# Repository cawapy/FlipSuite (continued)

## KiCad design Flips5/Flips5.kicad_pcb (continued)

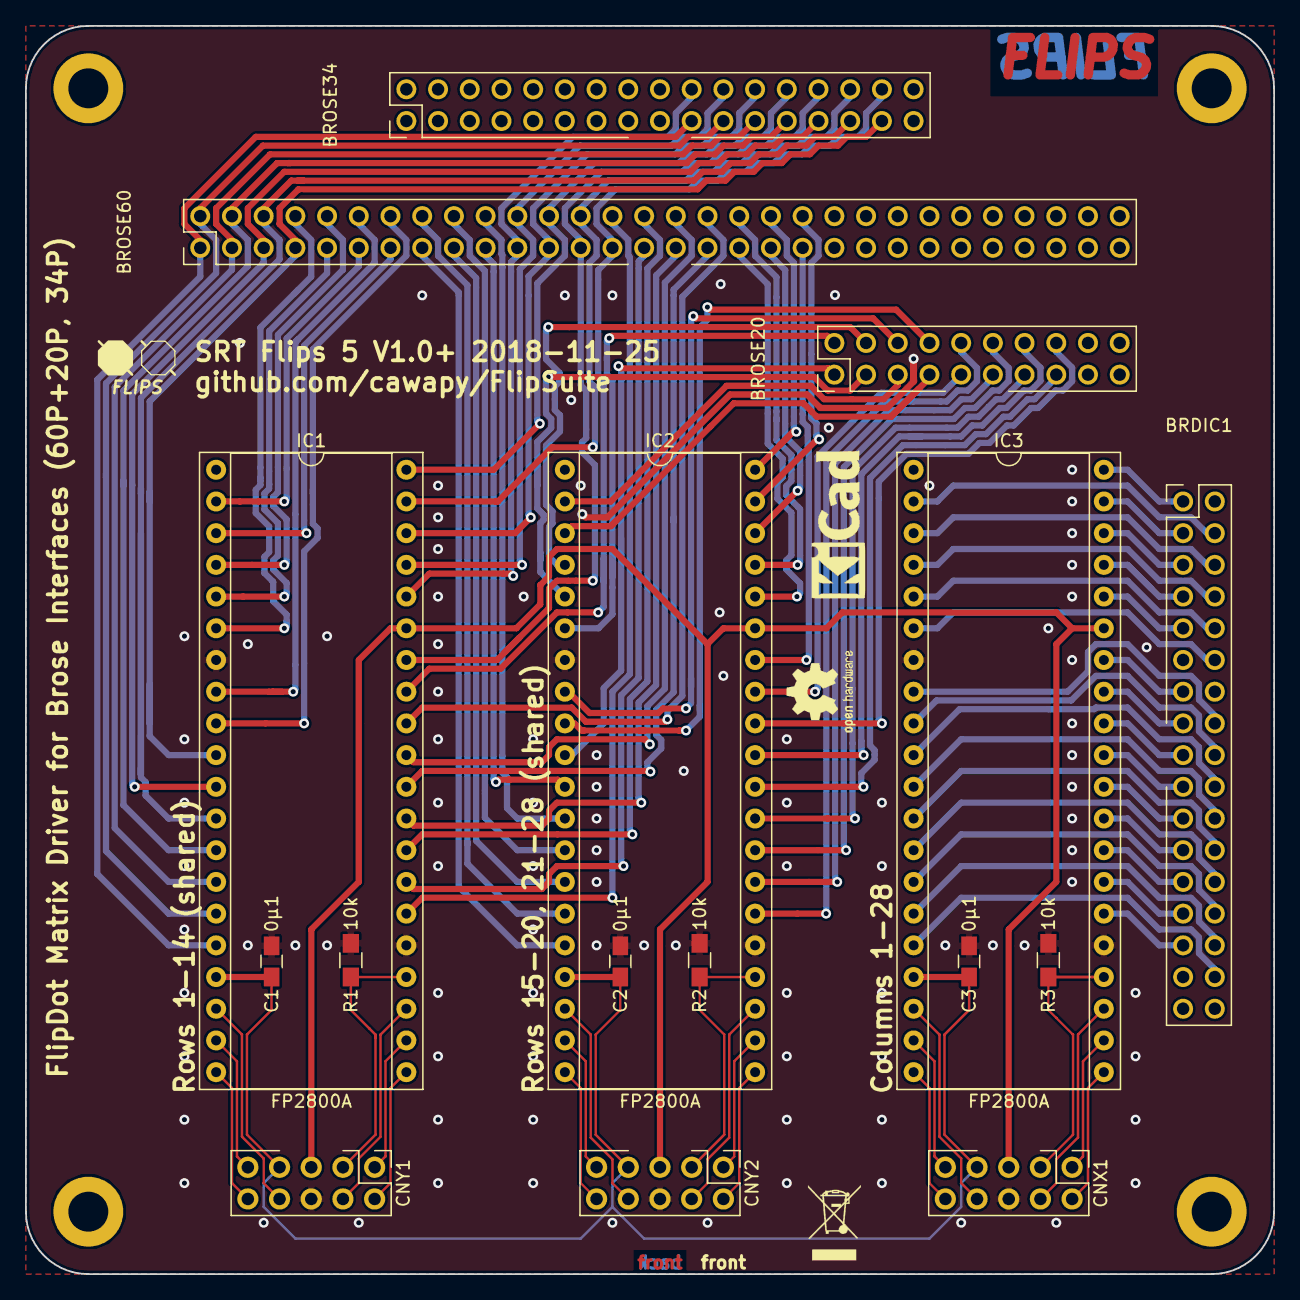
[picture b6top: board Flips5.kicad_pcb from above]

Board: 2 copper layers, 100.0 x 100.0 mm, 16 parts (0 on the bottom side), 108 nets.

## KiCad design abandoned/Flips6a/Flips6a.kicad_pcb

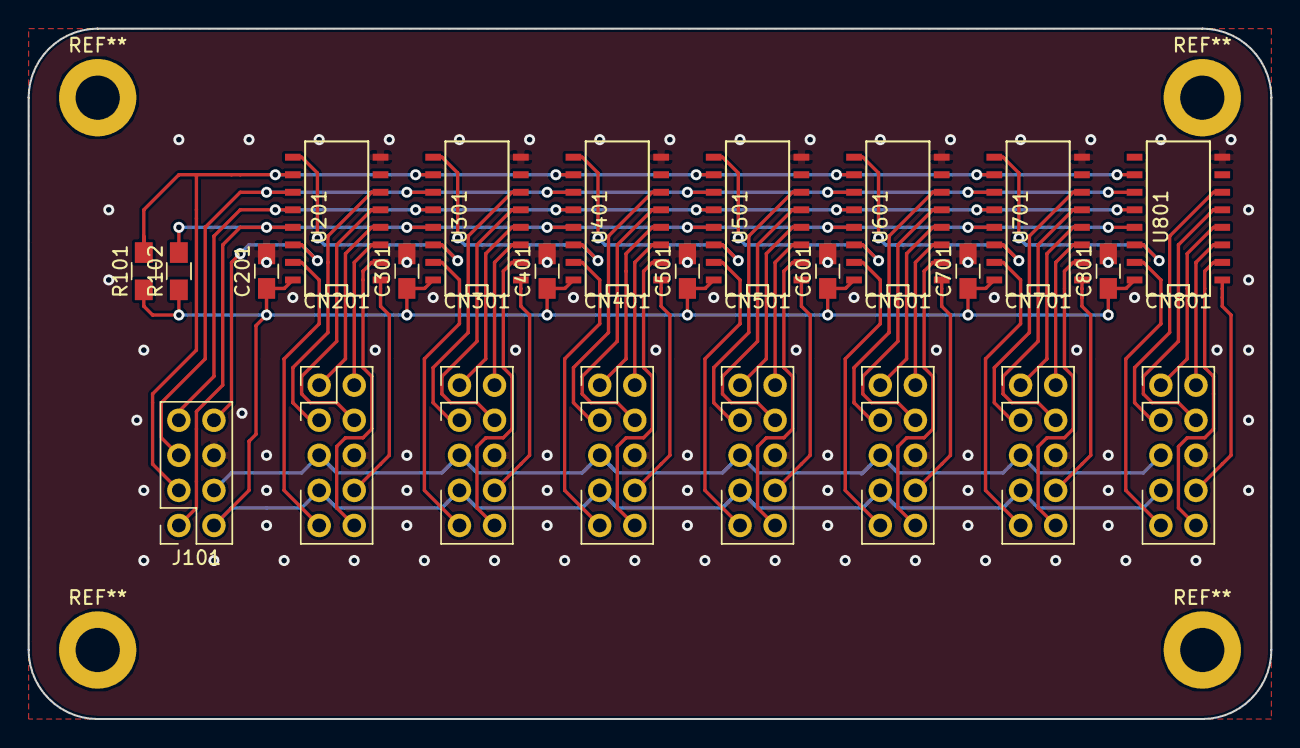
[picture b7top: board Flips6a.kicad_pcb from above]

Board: 2 copper layers, 90.0 x 50.0 mm, 24 parts (0 on the bottom side), 63 nets.

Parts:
C201, C301, C401, C501, C601, C701, C801: 0u1; C_0805_HandSoldering
CN201, CN301, CN401, CN501, CN601, CN701, CN801: UFP2810; Pin_Header_Straight_Shrouded_2x05_Pitch2.54mm
J101: Conn_02x04_Odd_Even; Socket_Strip_Straight_2x04_Pitch2.54mm
R101, R102: 10K; R_0805_HandSoldering
U201, U301, U401, U501, U601, U701, U801: 74HCT595; SO-16-N

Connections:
+5V: C201.1, C301.1, C401.1, C501.1, C601.1, C701.1, C801.1, CN201.7, CN301.7, CN401.7, CN501.7, CN601.7, CN701.7, CN801.7, J101.2, R101.1, R102.1, U201.16, U301.16, U401.16, U501.16, U601.16, U701.16, U801.16
+12V: CN201.5, CN301.5, CN401.5, CN501.5, CN601.5, CN701.5, CN801.5, J101.4
/ShiftRegister2/A0: CN201.9, U201.15
/ShiftRegister2/A1: CN201.8, U201.1
/ShiftRegister2/A2: CN201.10, U201.2
/ShiftRegister2/B0: CN201.2, U201.3
/ShiftRegister2/B1: CN201.1, U201.4
/ShiftRegister2/DATA: CN201.4, U201.5
/ShiftRegister2/DIN: J101.8, U201.14
/ShiftRegister2/EN: CN201.3, U201.6
/ShiftRegister3/A0: CN301.9, U301.15
/ShiftRegister3/A1: CN301.8, U301.1
/ShiftRegister3/A2: CN301.10, U301.2
/ShiftRegister3/B0: CN301.2, U301.3
/ShiftRegister3/B1: CN301.1, U301.4
/ShiftRegister3/DATA: CN301.4, U301.5
/ShiftRegister3/DIN: U201.9, U301.14
/ShiftRegister3/EN: CN301.3, U301.6
/ShiftRegister4/A0: CN401.9, U401.15
/ShiftRegister4/A1: CN401.8, U401.1
/ShiftRegister4/A2: CN401.10, U401.2
/ShiftRegister4/B0: CN401.2, U401.3
/ShiftRegister4/B1: CN401.1, U401.4
/ShiftRegister4/DATA: CN401.4, U401.5
/ShiftRegister4/DIN: U301.9, U401.14
/ShiftRegister4/EN: CN401.3, U401.6
/ShiftRegister5/A0: CN501.9, U501.15
/ShiftRegister5/A1: CN501.8, U501.1
/ShiftRegister5/A2: CN501.10, U501.2
/ShiftRegister5/B0: CN501.2, U501.3
/ShiftRegister5/B1: CN501.1, U501.4
/ShiftRegister5/DATA: CN501.4, U501.5
/ShiftRegister5/DIN: U401.9, U501.14
/ShiftRegister5/EN: CN501.3, U501.6
/ShiftRegister6/A0: CN601.9, U601.15
/ShiftRegister6/A1: CN601.8, U601.1
/ShiftRegister6/A2: CN601.10, U601.2
/ShiftRegister6/B0: CN601.2, U601.3
/ShiftRegister6/B1: CN601.1, U601.4
/ShiftRegister6/DATA: CN601.4, U601.5
/ShiftRegister6/DIN: U501.9, U601.14
/ShiftRegister6/EN: CN601.3, U601.6
/ShiftRegister7/A0: CN701.9, U701.15
/ShiftRegister7/A1: CN701.8, U701.1
/ShiftRegister7/A2: CN701.10, U701.2
/ShiftRegister7/B0: CN701.2, U701.3
/ShiftRegister7/B1: CN701.1, U701.4
/ShiftRegister7/DATA: CN701.4, U701.5
/ShiftRegister7/DIN: U601.9, U701.14
/ShiftRegister7/EN: CN701.3, U701.6
/ShiftRegister8/A0: CN801.9, U801.15
/ShiftRegister8/A1: CN801.8, U801.1
/ShiftRegister8/A2: CN801.10, U801.2
/ShiftRegister8/B0: CN801.2, U801.3
/ShiftRegister8/B1: CN801.1, U801.4
/ShiftRegister8/DATA: CN801.4, U801.5
/ShiftRegister8/DIN: U701.9, U801.14
/ShiftRegister8/EN: CN801.3, U801.6
GND: C201.2, C301.2, C401.2, C501.2, C601.2, C701.2, C801.2, CN201.6, CN301.6, CN401.6, CN501.6, CN601.6, CN701.6, CN801.6, J101.6, U201.8, U301.8, U401.8, U501.8, U601.8, U701.8, U801.8
RCLK: J101.7, U201.12, U301.12, U401.12, U501.12, U601.12, U701.12, U801.12
SRCLK: J101.5, U201.11, U301.11, U401.11, U501.11, U601.11, U701.11, U801.11
~OE: J101.1, R102.2, U201.13, U301.13, U401.13, U501.13, U601.13, U701.13, U801.13
~SRCLR: J101.3, R101.2, U201.10, U301.10, U401.10, U501.10, U601.10, U701.10, U801.10

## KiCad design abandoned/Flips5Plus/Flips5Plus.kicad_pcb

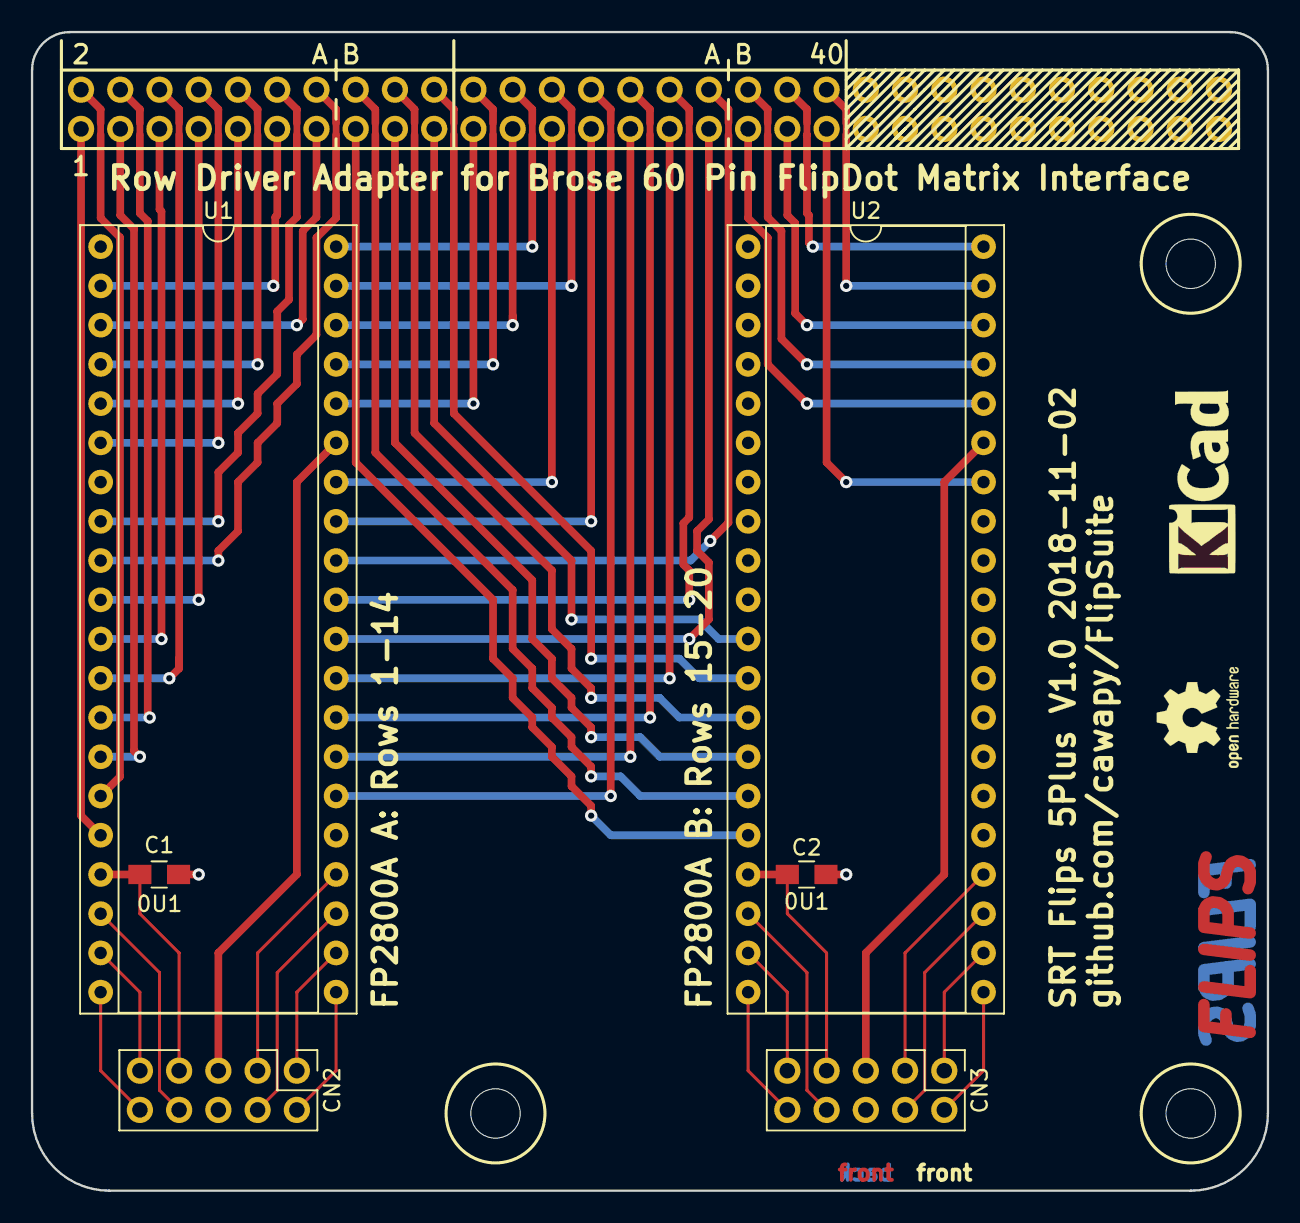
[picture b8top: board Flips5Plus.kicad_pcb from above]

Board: 2 copper layers, 80.0 x 75.0 mm, 7 parts (1 on the bottom side), 60 nets.

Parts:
C1, C2: 0U1; C_0805_HandSoldering
CN1: Conn_02x30_Odd_Even; Socket_Strip_Straight_2x30_Pitch2.54mm
CN2, CN3: UFP2810; Pin_Header_Angle_Shrouded_2x05_Pitch2.54mm
U1, U2: FP2800A; DIP-40_W15.24mm_Socket

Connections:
/L.A0: CN2.9, U1.19
/L.A1: CN2.8, U1.18
/L.A2: CN2.10, U1.20
/L.B0: CN2.2, U1.21
/L.B1: CN2.1, U1.22
/L.EN: CN2.3, U1.24
/L.GND: C1.1, CN2.6, U1.7, U1.25
/L.HV: CN2.5, U1.35
/L.POL: CN2.4, U1.23
/L.VCC: C1.2, CN2.7, U1.17
/R.A0: CN3.9, U2.19
/R.A1: CN3.8, U2.18
/R.A2: CN3.10, U2.20
/R.B0: CN3.2, U2.21
/R.B1: CN3.1, U2.22
/R.EN: CN3.3, U2.24
/R.GND: C2.2, CN3.6, U2.7, U2.25
/R.HV: CN3.5, U2.35
/R.POL: CN3.4, U2.23
/R.VCC: C2.1, CN3.7, U2.17
unnamed: CN1.1, U1.16
unnamed: CN1.2, U1.15
unnamed: CN1.3, U1.14
unnamed: CN1.4, U1.13
unnamed: CN1.5, U1.11
unnamed: CN1.6, U1.12
unnamed: CN1.7, U1.10
unnamed: CN1.8, U1.6
unnamed: CN1.9, U1.5
unnamed: CN1.10, U1.4
unnamed: CN1.11, U1.2
unnamed: CN1.12, U1.8
unnamed: CN1.13, U1.3
unnamed: CN1.14, U1.9
unnamed: CN1.15, U2.16
unnamed: CN1.16, U2.15
unnamed: CN1.17, U2.14
unnamed: CN1.18, U2.13
unnamed: CN1.19, U2.11
unnamed: CN1.20, U2.12
unnamed: CN1.21, U1.36
unnamed: CN1.22, U1.37
unnamed: CN1.23, U1.38
unnamed: CN1.24, U1.40
unnamed: CN1.25, U1.34
unnamed: CN1.26, U1.39
unnamed: CN1.27, U1.33
unnamed: CN1.28, U1.26
unnamed: CN1.29, U1.27
unnamed: CN1.30, U1.28
unnamed: CN1.31, U1.29
unnamed: CN1.32, U1.31
unnamed: CN1.33, U1.30
unnamed: CN1.34, U1.32
unnamed: CN1.35, U2.36
unnamed: CN1.36, U2.37
unnamed: CN1.37, U2.38
unnamed: CN1.38, U2.40
unnamed: CN1.39, U2.34
unnamed: CN1.40, U2.39

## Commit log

2018-08-27 Improve FPDriverPlug
    - Switch from DIP40 to DIP32
    - Use stronger traces for connections with relevant current
    - Use copper fill for GND
2018-08-27 Rework traces on FPDriverPlug
    - move non-GND traces to back layer
    - use direct non-45 degree traces for pass through connections
2018-08-27 changing 3d model to get illusion of dip40 socket
2018-08-27 fine tuning traces
2018-08-28 - Using DIP32 instead of DIP40 for FP2800A-Outputs - Shrinking Board to 80x55, re-aligning mounting holes to be in 5 mm raster - Labeling sheet and pcb plan - adding text and drawing on pcb
2018-08-29 adding project data to schematic and pcb
2018-08-29 removing leftover drawings on Eco2.User layer
2018-08-29 adding rudimentary labeling on copper layers
2018-10-28 0.2 of Flips4
    - Use IDC shrouded header
    - Add more space between IC and header
    - Center header
    - Remove round corners
    - Fix labels
2018-10-28 new kicadlib
2018-10-28 shrinking Flips4 to minimum
2018-10-28 adding optional pulldown for ENABLE
2018-10-29 Using angled IDC connector
2018-10-29 Rework silkscreen
2018-10-29 adding Flips4 label to front
2018-10-29 Adding Flips6 project with schematic
2018-10-29 switch resistor to 0805 package
2018-10-29 Switching to 0805 smd packages for Cs and Rs
2018-10-29 proper naming of active-low signals ~OE and ~SRCLR
2018-10-30 Adding first layout concept
2018-10-30 Finished routing for Fips6 first attempt
2018-10-30 Making shape 90x50, with mounting holes in 80x40 rectangle
2018-10-31 adding vias for GND
2018-10-31 fixing path of Flips6
2018-10-31 adding flips6b for 2x8 bit shift register control
2018-10-31 first attempt of Flips6b
2018-11-01 first attempt for Flips6b routed
2018-11-01 adding vias to Flips6b
2018-11-01 Rudimentary silk screen
2018-11-01 Updating IDC connector 3d models
2018-11-01 some deco
2018-11-01 adding Flips6c with schematics
2018-11-01 partial pcb layout / routing of Flips6c
2018-11-01 Fixing wrong wiring of DIN/DOUT
2018-11-01 finish tracing PCB for flips6c
2018-11-01 moving pullups into small gap, leaving space for text/labels
2018-11-01 minor tweaks
2018-11-01 rework silk screen
2018-11-01 cleanup traces
2018-11-01 changing trace widths
2018-11-01 adding readme for Flips6c
2018-11-01 Rename Flips6 to Flips6a
2018-11-01 renamed FPDriverPlug Flips4
2018-11-01 renamed Brose60Adapter to Flips5
2018-11-02 adding Flips5Plus
2018-11-02 configuring own kicad lib footprint library
2018-11-02 using ANGLED shrouded header
2018-11-02 using own UFP2810 connector
2018-11-02 flips 6c to use own UFP2810 connector
2018-11-02 switch flips 6a to use own UFP2810 connector
2018-11-02 Flips6b use UFP2810 connector
2018-11-02 fixing 8 pin connector
2018-11-02 improve 595 control traces
2018-11-02 improve 595 5v supply tracing
2018-11-02 reworking gnd vias
2018-11-02 adding logos and 3d models
2018-11-03 rework inscriptions
2018-11-03 rearranging mounting holes and symbols fixing measurements
2018-11-03 remove invalid mask line
2018-11-03 adjusting round corners
2018-11-03 setting up for plot/export
2018-11-03 toggling copper behind "K" of "KiCad" logo
2018-11-03 set flip current traces to 0.5mm
2018-11-03 made 12 V net .44 mm, but 5 V net standard 0.2 mm
2018-11-04 adding bypass capacitors
2018-11-04 More FP2800 info printed on Flips4
2018-11-04 adding description and pinout
2018-11-04 starting Flips7 for TransitMedia displays
2018-11-04 tracing flips7
2018-11-05 Using straight instead of angled IDC connector due to limited space on Brose display
2018-11-05 adding row driver share connectors
2018-11-05 optimize routing
2018-11-05 more re-routing
2018-11-06 rename row pins to /SY## and RY##
2018-11-06 fixing design rule to reflect new net names
2018-11-06 Adding links to PCB online viewer
2018-11-06 cloning Flips5Plus from Flips5X
2018-11-06 introducing Flips5X concept
2018-11-06 making board 10x10
2018-11-07 Using new 34P IDC connector for connecting column driver FP2800 onto display board
2018-11-07 adding 34P connector for 5x digit a 5x7 dots display
2018-11-10 new layout for FlipsX5
2018-11-10 less fragmented GND planes
2018-11-10 minor retracing
2018-11-10 adding pulldown for ENABLE
2018-11-10 writing 0μ1 instead of 0U1 for 0.1 micro farad
2018-11-10 adding R3 and 0μ1 value to PCB, including FP2800 values
2018-11-10 rename L.* and R.* to Y1.* and Y2.*
2018-11-10 renaming connectors
2018-11-10 fixing DIP connector assignment; adding vias
2018-11-10 adding flips6d based on flips6c
2018-11-11 Fixing 34 Pin interface pin mapping; renaming RYnn to ~RYnn
2018-11-11 adding 6th UFP2810 port CNX6
2018-11-11 Fixing values to read more friendly, including tech agnostic 74595
2018-11-12 allign grid origin to upper left corner
2018-11-12 new routing attempt (wip) for Flips7
2018-11-13 more tracing for Flips7 (still wip)
2018-11-13 Tracing column driver lines for Flips7
2018-11-13 single GND, VCC and HV; almost finish tracing
2018-11-13 GND on share connectors
2018-11-13 Fixing C values to 0µ1; connecting VCC of 3 units
2018-11-13 adding vias
2018-11-13 Adding silk and other deco
2018-11-13 Tuning traces
2018-11-14 Adding text
2018-11-14 setting grid origin
2018-11-14 Shifting board connector to get space for mounting pads
2018-11-14 Improve tracing
2018-11-14 moving connectors and adding 4th mounting pad
2018-11-14 moving text, adding lines to visually group driver ics and corresponding connectors
2018-11-14 Adding Flips Logo
2018-11-14 single GND, VCC, HV for Flips5X
2018-11-14 minor trace changes
2018-11-14 rerouting
2018-11-14 adding logo
2018-11-14 improve trace spacing
2018-11-14 update timestamp
2018-11-15 narrow tracing of Flips6c
2018-11-15 finer routing
2018-11-15 fixing missing VCC connection
2018-11-16 adding pull downs for ENABLE pins
2018-11-16 rename some symbols
    rename L.## and R.## nets to Y1.## and Y2.##
    rename CN1 and CN2 to SHR1 and SHR2
    rename U1/2/3 to IC1/2/3
2018-11-16 update jumper description
2018-11-16 renaming footprint references
    U1/2/3 to IC1/2/3
    swap R1 and R2
2018-11-16 Rename Flips6c description
2018-11-16 Rename U1/2/3 to IC1/2/3
2018-11-16 Replace mounting holes: use variants with pad
2018-11-16 moving abandoned project, renaming remaining
2018-11-16 adjust titles and labels
2018-11-16 updating page labels
2018-11-16 Switching back to V0.9
2018-11-18 adding shift register pin mapping
2018-11-18 Changing pin names in mapping table on back side silk screen
2018-11-18 move pcb to (2 in | 2 in)
2018-11-19 removing margin drawings
2018-11-19 fix footprint of 74595 to SOIC-16_3.9x9.9mm_Pitch1.27mm
2018-11-19 Correcting some traces
2018-11-20 Adding Rows 21-28 (extra connector; preliminary pin assignment)
2018-11-20 adding "+20P" in silk screen and descriptions; adding 3d model for row driver; cleaning up traces
2018-11-21 sorting traces
2018-11-22 Fix icon footprint positions
2018-11-22 change traces
2018-11-22 finer ground planes
2018-11-22 adding pinout of CNX/CNY connectors
2018-11-22 adding pulldowns for enable pins
2018-11-22 more ground plane friendly tracing
2018-11-22 new placement of logos
2018-11-22 adding pinout
2018-11-23 Prepare release
2018-11-25 Adding gerbers and aux files for Release V1.0 of Flips5/6/7
2018-11-25 fixing huge solder mask spacing
2018-11-25 fixing flips logo
2018-11-25 Udating version to post-V1.0
2018-11-26 adding empty flips8
2018-11-26 starting Flips8 - NCV7708 based Annax Display Driver
2018-11-27 updating readme and pcb markdown files
2018-11-27 adding some description
2018-11-27 Typos and clarity in description.md
2018-11-28 proceed with Flips8
2018-11-29 finish initial routing of Flips8
2018-12-01 Place FP2800As' bypass capacitors and EN-pulldowns to fit in Dip40 socket
2018-12-01 more systematic tracing for Flisp8
2018-12-01 reposition ncv7708 of Flisp8
2018-12-01 more cleanup on pcb
2018-12-02 rearrange connector and decoder; move 'bus' away from board edge pt. 1
2018-12-02 fixing supply connection between ICs and capacitors
2018-12-02 adding bypass capacitor for decoder in flips
2018-12-10 Fix wrong labels of Flips6 uP connector: LAT <--> CLK
2018-12-10 rename RST to CLR
2018-12-13 Adding Flips software library
2018-12-13 Fix software folder structure to get using library work
2018-12-14 use fixed tpluc
2018-12-14 update readme - tests pending
2018-12-16 Adding Brose connector pins
2018-12-16 Change headings in description
2018-12-16 Adding Transit Media Connector Pins
2018-12-16 Rename pins to include leading zero if single digit only
2018-12-16 Adding hint for X04 on 14 column board
2018-12-16 Explain pins
2018-12-16 Small iprovement to traces
2018-12-16 preparing doc schematics
2018-12-21 fixing leftover trace
2019-01-04 Demo for 5 digit a 5x7 display "с новым годом"
2019-01-04 Update readme with known issues and some test success
2019-01-04 Reformatting recent changes to Readme
2019-01-04 Fixing links to commits in Readme
2019-01-04 new tpluc version
2019-01-07 update readme after successful test of 28x24 display on Flips5
2019-01-08 adding flips6-flips5 diagrams
2019-01-08 Update Readme
    * Adding tested configuration 28x16
    * Linking to system diagrams
2019-01-08 Adding option to not equip Cs and Rs of Flips5
2019-01-09 adding transit media system diagrams
2019-01-09 update readme regarding state of flips5
2019-01-09 adding minimal configurations
2019-01-09 rework brose configurations
2019-01-09 Rename links for Flips5 system diagrams
2019-01-12 update readme for transit media / flips7 success
2019-01-23 wip for selfMade7x28
2019-01-24 Replace DivMod by / and %
2019-01-24 adding optional relax phase (driving enable low for tRelax)
2019-01-24 introducing Flips6Skeleton and Flips65
2019-01-24 fix flips65 rowmapper name
2019-01-24 prepare custom 7x28 display and flips67
2019-01-24 Taking into account inverse polarity boards
2019-01-24 removing reset from 595 shift register and usage in flips
2019-01-27 Adding draft of Flips15
2019-01-27 rework Flips15 draft
2019-01-27 Flips15 to only use 1 unit
2019-01-27 experimenting with solder jumpers at BRDIC1 connector
2019-01-29 adding traces for flips 15
2019-01-31 more traces for flips15
2019-02-01 more tracing in flips15
2019-02-01 adding fill for flips15
2019-02-02 more tracing with overlapping connectors
2019-02-02 tracing Flips15
2019-02-02 Adding more solder jumpers to overlapping pins of BRDIC1 and BROSE34
2019-02-02 more tracing Flips15
2019-02-03 adding mounting holes, more traces
2019-02-03 move driver ics to get more space for decoders and control connector
2019-02-03 move drivers closer to connector
2019-02-03 preparing control wires
2019-02-03 placing decoders
2019-02-03 Adding control wires - removing control for channel 0 - placing capacitor
2019-02-03 Connecting supplies of drivers and decoder
2019-02-03 more control lines
2019-02-03 update gnd plane
2019-02-04 connecting enable lines of 8 decoders
2019-02-04 moving pcb to get space for upper right mounting hole
2019-02-05 Finish remaining connection on Flips15
2019-02-05 improve traces
2019-02-05 minor changes in traces
2019-02-05 Simplify traces
2019-02-05 Fixing alignment of board to 0.025 in grid
2019-02-05 better GND
2019-02-05 better ground plane
2019-02-05 arranging silk screen
2019-02-06 more silk screen (use more compact IC values)
2019-02-06 hiding BRDIC1 connector 3d model
2019-02-06 adding support for optional COM pin at BRDIC1
2019-02-07 change text for optional inverter
2019-02-07 re-annotating to get more compact part numbers
2019-02-07 adjust silk screen
2019-02-23 adding experimental Flips10 for replacing FP2800A
2019-02-23 splitting Flips10 into driver and base
2019-02-23 remove unused stuff for base and driver
2019-02-23 using own component SR28GR as connector for Flips10
2019-02-24 progress for flips10 base
2019-03-01 adding Flips9
2019-03-04 prepare traces of flips9
2019-03-04 Rotate connectors CN1,2
2019-03-04 adding extra 16 pin connector instead of reusing 24-pin connector
2019-03-06 routed more traces
2019-03-06 finish flips9 routing
2019-03-07 fixing GND THT pad orientation
2019-03-07 compactify traces
2019-03-08 adding rows 25-32
2019-03-09 compactify driver traces
2019-03-11 finish routing
2019-03-11 improve routing
2019-03-11 Adding capacitors, moving main decoder
